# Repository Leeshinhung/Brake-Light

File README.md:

# 煞車燈設計(v2)
 ## Schmedic 電路設計

 ## PCB 設計圖

 ## 3D Model
1. 正面

2. 背面

 ## 實體照片

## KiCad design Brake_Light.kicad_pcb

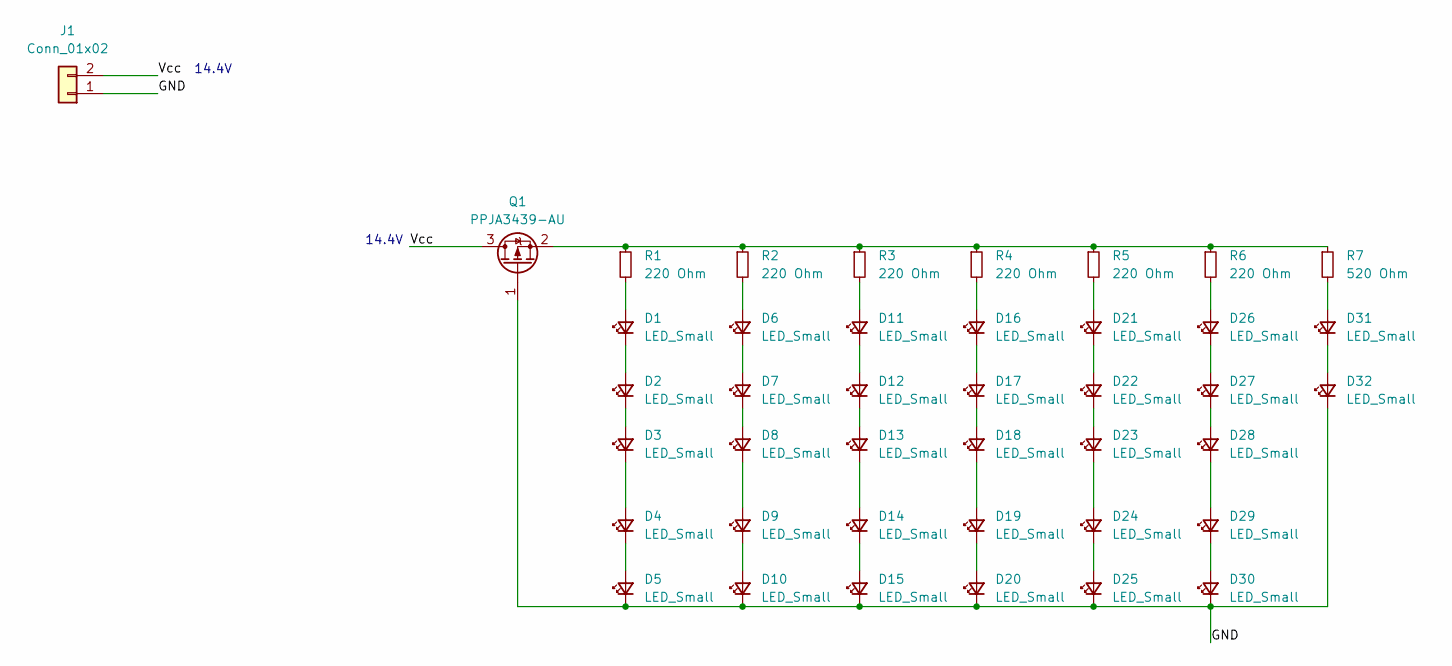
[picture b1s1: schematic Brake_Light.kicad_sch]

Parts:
D1, D2, D3, D4, D5, D6, D7, D8, D9, D10, D11, D12, D13, D14, D15, D16, D17, D18, D19, D20, D21, D22, D23, D24, D25, D26, D27, D28, D29, D30, D31, D32: LED_Small; LED_0805_2012Metric
J1: Conn_01x02; JST_XH_B2B-XH-A_1x02_P2.50mm_Vertical
Q1: PPJA3439-AU; SOT-23
R1, R2, R3, R4, R5, R6: 220 Ohm; R_0805_2012Metric
R7: 520 Ohm; R_0805_2012Metric

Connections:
/GND: D5.1 (K), D10.1 (K), D15.1 (K), D20.1 (K), D25.1 (K), D30.1 (K), D32.1 (K), J1.1, Q1.1 (G)
/Vcc: J1.2, Q1.3 (D)
unnamed: D1.2 (A), R1.2
unnamed: D1.1 (K), D2.2 (A)
unnamed: D2.1 (K), D3.2 (A)
unnamed: D3.1 (K), D4.2 (A)
unnamed: D4.1 (K), D5.2 (A)
unnamed: D6.2 (A), R2.2
unnamed: D6.1 (K), D7.2 (A)
unnamed: D7.1 (K), D8.2 (A)
unnamed: D8.1 (K), D9.2 (A)
unnamed: D9.1 (K), D10.2 (A)
unnamed: D11.2 (A), R3.2
unnamed: D11.1 (K), D12.2 (A)
unnamed: D12.1 (K), D13.2 (A)
unnamed: D13.1 (K), D14.2 (A)
unnamed: D14.1 (K), D15.2 (A)
unnamed: D16.2 (A), R4.2
unnamed: D16.1 (K), D17.2 (A)
unnamed: D17.1 (K), D18.2 (A)
unnamed: D18.1 (K), D19.2 (A)
unnamed: D19.1 (K), D20.2 (A)
unnamed: D21.2 (A), R5.2
unnamed: D21.1 (K), D22.2 (A)
unnamed: D22.1 (K), D23.2 (A)
unnamed: D23.1 (K), D24.2 (A)
unnamed: D24.1 (K), D25.2 (A)
unnamed: D26.2 (A), R6.2
unnamed: D26.1 (K), D27.2 (A)
unnamed: D27.1 (K), D28.2 (A)
unnamed: D28.1 (K), D29.2 (A)
unnamed: D29.1 (K), D30.2 (A)
unnamed: D31.2 (A), R7.2
unnamed: D31.1 (K), D32.2 (A)
unnamed: Q1.2 (S), R1.1, R2.1, R3.1, R4.1, R5.1, R6.1, R7.1

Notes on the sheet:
14.4V

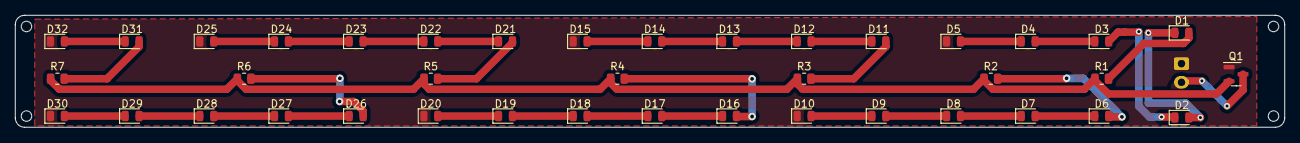
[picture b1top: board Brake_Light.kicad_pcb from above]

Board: 2 copper layers, 170.0 x 15.0 mm, 41 parts (1 on the bottom side), 35 nets.
